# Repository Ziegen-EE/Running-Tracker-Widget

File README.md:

# Running Tracker Widget  
*A compact Arduino-based wearable for tracking pace, distance, and run duration.*

---

## Overview
The **Running Tracker Widget** is a portable, battery-powered device designed to measure and display **running metrics** such as **pace**, **distance**, and **elapsed time**.  
Built around the **Arduino Pro Mini**, this system integrates GPS positioning, user controls, and a display interface to deliver accurate real-time tracking data in a lightweight form factor.  

This project highlights hands-on skills in **embedded systems**, **circuit design**, and **hardware integration**, forming a complete end-to-end electrical engineering prototype.

---

## System Features
- **Arduino Pro Mini Core** – Compact 5V microcontroller board for low-power applications  
- **Adafruit Ultimate GPS Module** – Provides accurate positional data (lat/lon, altitude, speed, and time)  
- **LCD Display with Adjustable Resistor** – Displays pace, distance, and time in real-time  
- **Pololu LV Power Switch** – Enables safe and efficient power management for battery use  
- **User Input Buttons** – Right-angle momentary push buttons for start/stop and mode navigation  
- **Passive Components** – Decoupling capacitors and precision resistors for signal stability and protection  
- **9V Battery Snap Connector** – Supports portable power input with quick connection  

---

## Bill of Materials (BOM)

You can view the full interactive BOM spreadsheet here:  
👉 [**Running Tracker BOM – Google Sheets**](https://docs.google.com/spreadsheets/d/1CWu7IO52Xdz1FhUTgCzN4FMrNsjh3O-xI5pumeO5So4/edit?usp=sharing)

| # | Component | Manufacturer | MPN | Qty | Description / Notes |
|---|-----------|--------------|------|-----|----------------------|
| 1 | Arduino Pro Mini Socket | SparkFun | DEV-11113 | 1 | 5V, 16MHz, core microcontroller board |
| 2 | Adafruit Ultimate GPS | Adafruit | 746 | 1 | High-accuracy GPS module with integrated antenna |
| 3 | Pololu LV Power Switch | Pololu | 2808 | 1 | Low-voltage switch for efficient battery control |
| 4 | LCD + Variable Resistor | Adafruit | 181 | 1 | Display and control interface |
| 5 | Right Angle Push Button | C&K | 611-KSS223GLFG | 3 | User input buttons |
| 6 | Capacitor 10µF | TAIYO YUDEN | MCASL21GBB7106KTNA01 | 1 | Power line stabilization |
| 7 | Capacitor 0.1µF | KYOCERA AVX | KAM21BR71H104JM | 1 | Signal filtering |
| 8 | Resistor 220Ω | Panasonic | ERJ-S06F2200V | 1 | Current limiting |
| 9 | Resistor 10kΩ | KOA Speer | SG73P2ARTTD103G | 3 | Voltage division and logic pull-ups |
| 10 | 9V Battery Snap | Bourns | LS-00033 | 1 | Power supply connector |

---

## Functional Overview
1. **GPS Data Acquisition:** The Adafruit GPS module provides NMEA data for time, position, and velocity.  
2. **Microcontroller Processing:** The Arduino Pro Mini calculates pace and distance based on GPS data.  
3. **User Interaction:** Push buttons allow start/stop control and data viewing.  
4. **Display Output:** The LCD module shows real-time run statistics.  
5. **Power Regulation:** The Pololu switch ensures stable and safe power control from a 9V source.

---

## Technical Specifications
- **Operating Voltage:** 5V  
- **Input Power:** 9V battery (via snap connector)  
- **Microcontroller:** ATmega328P (Arduino Pro Mini)  
- **Display Interface:** Parallel/Serial LCD  
- **Sensors:** GPS (Adafruit Ultimate GPS)  
- **User Inputs:** 3x push buttons  
- **Enclosure:** Compatible with 3D-printed housing or handheld casing  

---

## Development Tools
- **IDE:** Arduino IDE  
- **Language:** C/C++  
- **Libraries:** `Adafruit_GPS`, `LiquidCrystal`, `SoftwareSerial`  
- **Simulation / Schematic:** KiCad or EasyEDA  

---

## Future Enhancements
- Add accelerometer or IMU sensor for step-based distance correction  
- Integrate Bluetooth for mobile sync  
- Log data to microSD for long-term performance tracking  
- Optimize firmware for lower power consumption

---

### PCB Manufacturing
The PCB layout and Gerber files were created following **[3DayPCBs](https://3daypcbs.com)** standard manufacturing specifications.  
Key parameters include:
- 1.6 mm board thickness  
- 1 oz copper weight  
- 6 mil minimum trace/space  
- Standard FR-4 substrate  
- Through-hole and SMD mixed design  

Compatibility with other PCB manufacturers may require DRC rule adjustments.

---

## License
This project is licensed under the [MIT License](LICENSE).  
Feel free to use and modify with attribution.

**PCB Design Notice:**  
All PCB and Gerber files included in this repository are designed according to **[3DayPCBs](https://3daypcbs.com)** manufacturing specifications, including board thickness, copper weight, trace width, and drill tolerances.  
Users adapting the design for other manufacturers should verify compatibility and adjust design rules accordingly.

---

## Acknowledgments

This project makes use of the [Arduino KiCad Library](https://github.com/Alarm-Siren/arduino-kicad-library)  
by **Alarm-Siren**, distributed under the [MIT License](https://github.com/Alarm-Siren/arduino-kicad-library/blob/main/LICENSE).

The library was used for schematic and footprint references during PCB design.

---

## Sponsorship & Support

This project is proudly supported by the  
**[School District 38 CTE (Career & Technical Education) Program](https://www.lewispalmer.org/cte)**.  

Their sponsorship provided access to electronic components, fabrication tools, and resources essential for the development and testing of the Activity Tracker Widget.  
Special thanks to the instructors and staff who promote hands-on STEM and engineering education.

## PCB Manufacturing Support

PCB fabrication for this project can be reliably handled by **PCBWay**, a professional PCB manufacturing and assembly service widely used for prototyping and medium to large-scale production.

PCBWay is well-suited for projects like my **Running Tracker Widget**, which combine through-hole and SMD components in a compact embedded design. Their capabilities support iterative hardware development and manufacturing constraints common in wearable and portable electronics.

### Relevant Capabilities
- Standard **FR-4 PCB fabrication** with configurable thickness and copper weight  
- Support for **mixed through-hole and SMD designs**  
- Optional **PCB assembly (PCBA)** for populated boards  
- Fast turnaround times suitable for prototyping and validation  

Design files created for this project are adapted for 3DayPCBs, although manufacturing specifications are well within their capabilities!!!

Additional information is available at:  
👉 **https://www.pcbway.com**

PCBWay actively supports open-source hardware projects and educational engineering development.

---

## Author
**[Ziegen Ludwig]**  
Electrical Engineering Student | Embedded Systems Developer  
🔧 *Focused on IoT, microcontroller design, and wearable electronics.*

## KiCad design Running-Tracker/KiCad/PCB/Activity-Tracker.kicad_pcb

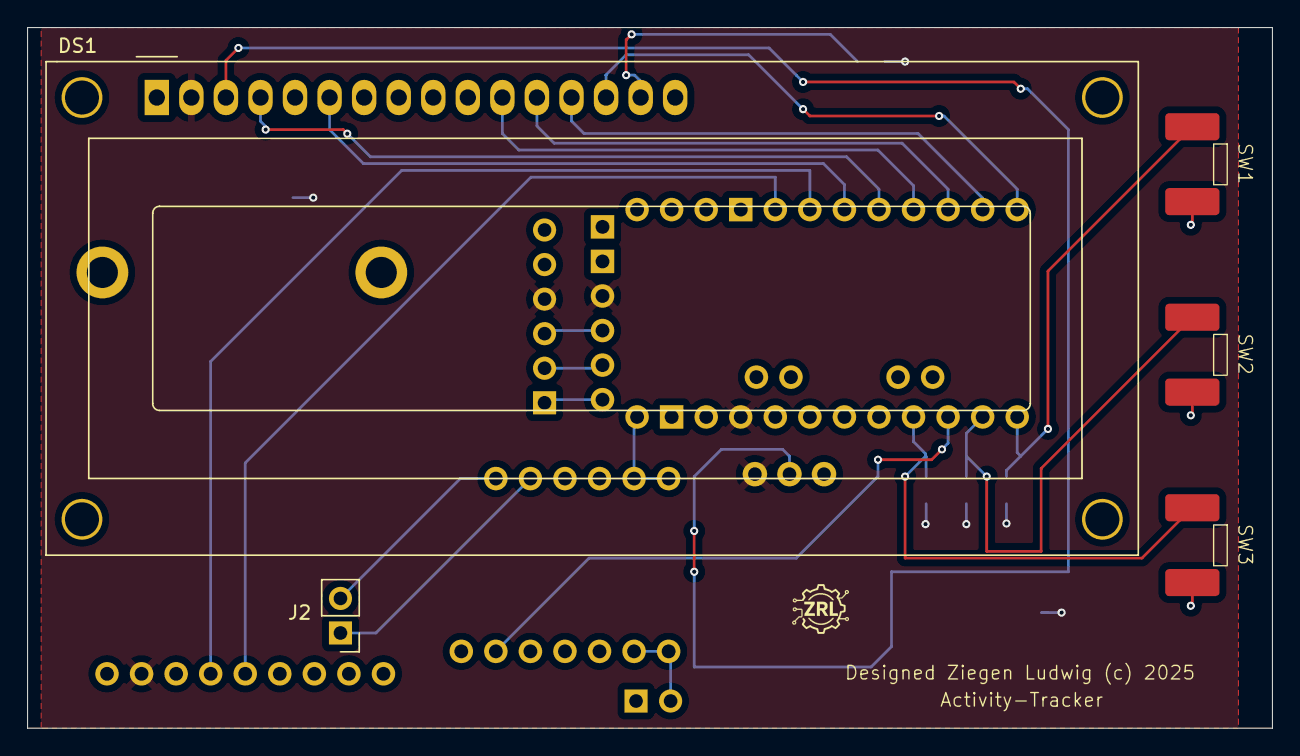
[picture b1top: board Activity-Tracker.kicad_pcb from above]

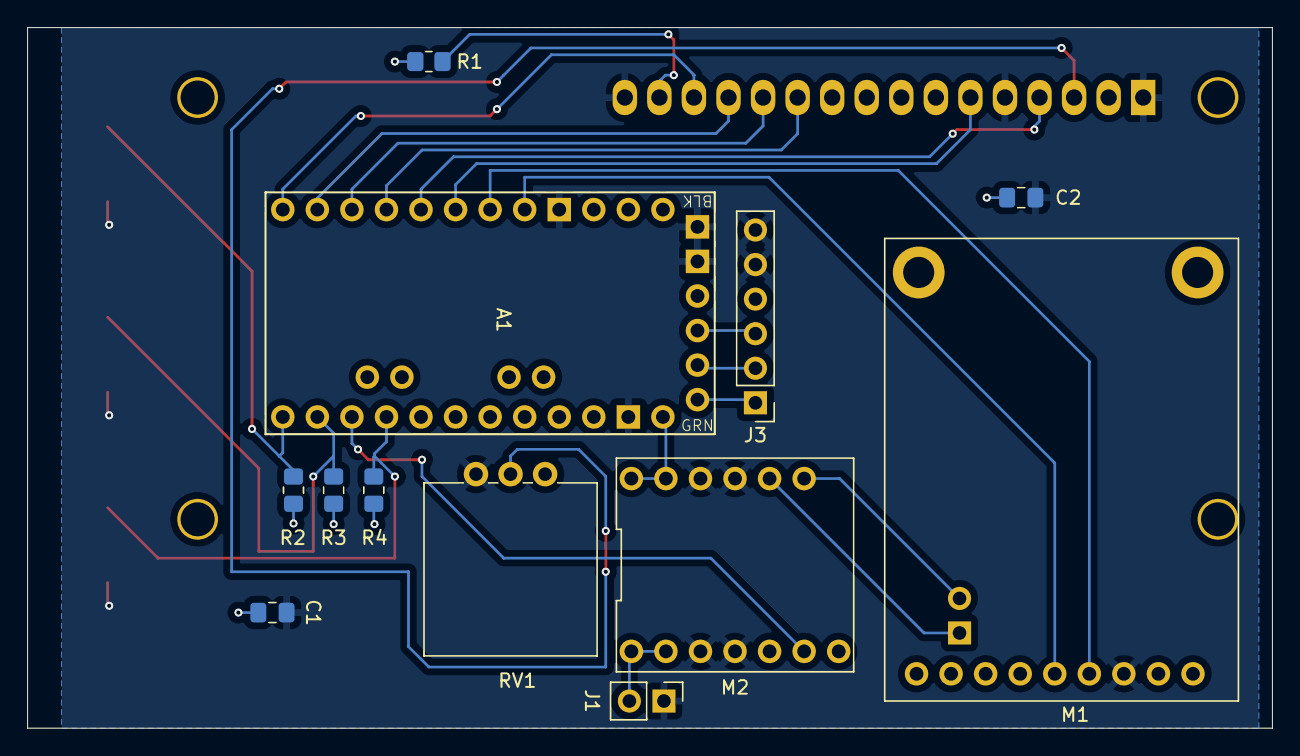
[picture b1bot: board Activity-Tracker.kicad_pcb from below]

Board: 2 copper layers, 91.5 x 51.5 mm, 17 parts (12 on the bottom side), 23 nets.

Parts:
A1: Arduino_Pro_Mini_Socket
C1: 10 uf; C_0805_2012Metric_Pad1.18x1.45mm_HandSolder
C2: .1 uf; C_0805_2012Metric_Pad1.18x1.45mm_HandSolder
DS1: WC1602A
J1, J2: Conn_01x02_Socket; PinHeader_1x02_P2.54mm_Vertical
J3: Conn_01x06_Pin; PinHeader_1x06_P2.54mm_Vertical
M1: GPS; Adafruit Ultimate GPS
M2: Power Module; Pololu LV Power Switch
R1: 220; R_0805_2012Metric_Pad1.20x1.40mm_HandSolder
R2, R3, R4: 10k; R_0805_2012Metric_Pad1.20x1.40mm_HandSolder
RV1: 10K; Potentiometer_Vishay_148-149_Single_Vertical
SW1, SW2, SW3: SW_Push; KSS223G LFG

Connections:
+5V: A1.Vcc1 (Vcc), A1.Vcc2 (Vcc), C1.1, C2.1, DS1.2 (VDD), J3.4, M1.8 (VIN), R1.1, R2.1, R3.1, R4.1, RV1.3
/BTN_1: A1.D10 (D10_CS), R2.2, SW1.1
/BTN_2: A1.D11 (D11_MOSI), R3.2, SW2.1
/BTN_3: A1.D13 (D13_SCK), R4.2, SW3.1
/GPS_RX: A1.D3 (D3_INT1), M1.6 (RX)
/GPS_TX: A1.D2 (D2_INT0), M1.5 (TX)
/LCD_D4: A1.D6, DS1.11 (D4)
/LCD_D5: A1.D7, DS1.12 (D5)
/LCD_D6: A1.D8, DS1.13 (D6)
/LCD_D7: A1.D9, DS1.14 (D7)
/LCD_E: A1.D4, DS1.6 (E)
/LCD_LDEP: DS1.15 (LED(+)), R1.2
/LCD_RS: A1.D5, DS1.4 (RS)
/PWR_OFF: A1.D12 (D12_MISO), M2.6 (OFF)
/VBAT: J1.2, M2.1 (VIN), M2.2 (VIN)
/VRAW: A1.RAW, M2.13 (VOUT), M2.14 (VOUT)
GND: A1.GND1 (GND), A1.GND2 (GND), A1.GND4 (GND), A1.GND5 (GND), C1.2, C2.2, DS1.1 (VSS), DS1.5 (R/W), DS1.16 (LED(-)), J1.1, J3.5, J3.6, M1.7 (GND), M2.3 (GND), M2.4 (GND), M2.11 (GND), M2.12 (GND), RV1.1, SW1.2, SW2.2, SW3.2
unnamed: A1.DTR (~DTR), J3.1
unnamed: DS1.3 (VO), RV1.2
unnamed: J2.1, M2.10 (B)
unnamed: J2.2, M2.9 (A)
unnamed: A1.TXO, J3.2
unnamed: A1.RXI, J3.3

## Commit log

2025-11-10 Create foler
2025-11-10 Add direct csv file
2025-11-10 Create Placeholder
2025-11-10 add Schematic PNG
2025-11-10 Rename image.png to schematic.png
2025-11-10 Rename Screenshot 2025-11-09 105746.png to 2D_PCB.png
2025-11-10 Rename image_2025-11-09_171721083.png to 3D_PCB.png
2025-11-10 Update LICENSE
2025-11-17 Create temp
2025-12-16 Rename Activity-Tracker to Running-Tracker
2025-12-26 Add PCBWay support section to README
    Expanded the README to include detailed information about PCBWay's capabilities and support for the project, emphasizing its suitability for the Running Tracker Widget. Forgot to push.

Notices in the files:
Running-Tracker/KiCad/PCB/Activity-Tracker.kicad_pcb:
Designed Ziegen Ludwig (c) 2025
